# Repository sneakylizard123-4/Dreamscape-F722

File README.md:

# Dreamscape F722
Dreamscape F722 is an open-hardware STM32-based flight controller designed for FPV and custom drone platforms. It targets high-performance firmware such as Betaflight, iNav, and ArduPilot while remaining developer-friendly for experimentation and customization. The design focuses on a powerful MCU, robust connectivity, and support for a wide range of peripherals to enable advanced flight control features and future expansion.

# Features
## MCU
- STM32 F722RET6
- 32-bit ARM Cortex-M7 CPU
- Up to 216 MHz clock speed
- Large memory for advanced firmware features
- Compatible with Betaflight/iNav/ArduPilot

## Power System
- 5V input with built-in 3.3v regulator
- Power distribution for peripherals
- USB Power support
- Protection for USB

## Connectivity
- USB Type-C for programming and communication
- Multiple UART ports for telemetry and peripherals
- I2C bus for sensors and accessories
- SPI interface for high-speed communication
- SWD debugging port

## Sensors
- ICM-42688-P 6-axis IMU (3-axis gyroscope + 3-axis accelerometer) via SPI for precise flight control and low latency
- BMP280 barometer for altitude sensing
- Optional external sensor support via I2C

## Flight Control Outputs
- 8 PWM outputs
- Supports DSHOT, Oneshot, and standard PWM protocols
- Compatible with individual ESCs or 4-in-1 ESCs

## Radio / Receiver Support
- CRSF (Crossfire) support for long-range control
- SBUS support for standard RC receivers
- PPM support for legacy receivers
- Support for external radio modules via UART

## Status & Indicators
- Power LED
- User LED
- Boot/Status LED

## Expansion & Peripherals
- GPS module support via UART
- Telemetry Radios
- VTX control (SmartAudio or Tramp)
- Buzzer for audible alerts
- Camera control
- External sensor support (e.g., magnetometer, external barometer)

## Physical Design
- Compact flight-controller form factor (30x30mm)
- Standard mounting pattern
- Designed for custom drones

## Development Friendly
- Open-source hardware design files
- Open-source firmware support (Betaflight, iNav, ArduPilot)
- Easy debugging with SWD port

## Planned Future Features
- Integrated ELRS receiver
- Dual-Band telemetry support
- Advanced Sensor suite
- Power monitoring improvements
- Integrated OSD support

# Specifications
## Core Specifications
### MCU
- MCU: STM32 F722RET6
- Architecture: ARM Cortex-M7
- Clock Speed: Up to 216 MHz
- Flash Memory: 512 KB
- RAM: 256 KB
- Hardware Floating Point Unit (FPU)

### Inertial Measurement Unit (IMU)
- IMU: ICM-42688-P
- HIgh-speed SPI bus for low latency
- Optimied placement for reduced vibration noise

### Power System
- Input Voltage: 5V (via USB or power distribution)
- Built-in 3.3V regulator for peripherals
- USB Power support with protection
- Power distribution for connected peripherals

## I/O and Connectivity
### UART Ports
- UART1: Receiver 
- UART2: GPS module
- UART3: Telemetry
- UART4: VTX Control
- UART5: Reserved for future expansion

### SPI Interfaces
- SPI1: IMU (ICM-42688-P)
- SPI2: Reserved for future sensor expansion

### I2C Bus
- I2C bus available for peripherals such as magnetometers, external barometers, etc.

### SWD
- SWD header for debugging and firmware development

## Motor Outputs
- Up to 8 PWM outputs
- Suppored Protocols:
  - DShot150/300/600
  - OneShot
  - Multishot
  - Standard PWM
  - Compatible with individual ESCs or 4-in-1 ESCs

## Receiver Support
- CRSF (Crossfire) support for long-range control
- SBUS support for standard RC receivers
- PPM support for legacy receivers
- Support for external radio modules via UART

## Additional Peripherals
- Buzzer output
- LED Strip output
- Camera control
- VTX control (SmartAudio or Tramp)

## Status Indicators
- Power LED
- User LED
- Boot/Status LED

## Physical Dimensions
- Size: 30x30mm
- Board Layers: 4
- PCB Thickness: 1.6mm
- Copper Weight: 1oz
- Dimensions: Standard flight controller mounting pattern

## Firmware Compatibility
- Designed for compatibility with Betaflight, iNav, and ArduPilot
- Open-source firmware support for customization and development

## Development Features
- Open Hardware design
- Full SWD debugging support
- Compatible with ST-Link Programmers
- Designed for experimentation and customization

## Planned Future Features
- Integrated ELRS receiver for long-range control
- Dual-Band telemetry support for improved communication
- Advanced Sensor suite including magnetometer and external barometer support
- Integrated ESC for AIO support
- Integrated OSD support for on-screen display of flight information
- Improved powwer monitoring with current sensing and voltage monitoring

# Firmware Building
````bash
cd ~/Dreamscape-F722/firmware/betaflight/betaflight
make configs
make DREAMSCAPEF722
````

# Blender Render:

# Schematics & PCB view

# prices

# LCSC (Hand Soldering)

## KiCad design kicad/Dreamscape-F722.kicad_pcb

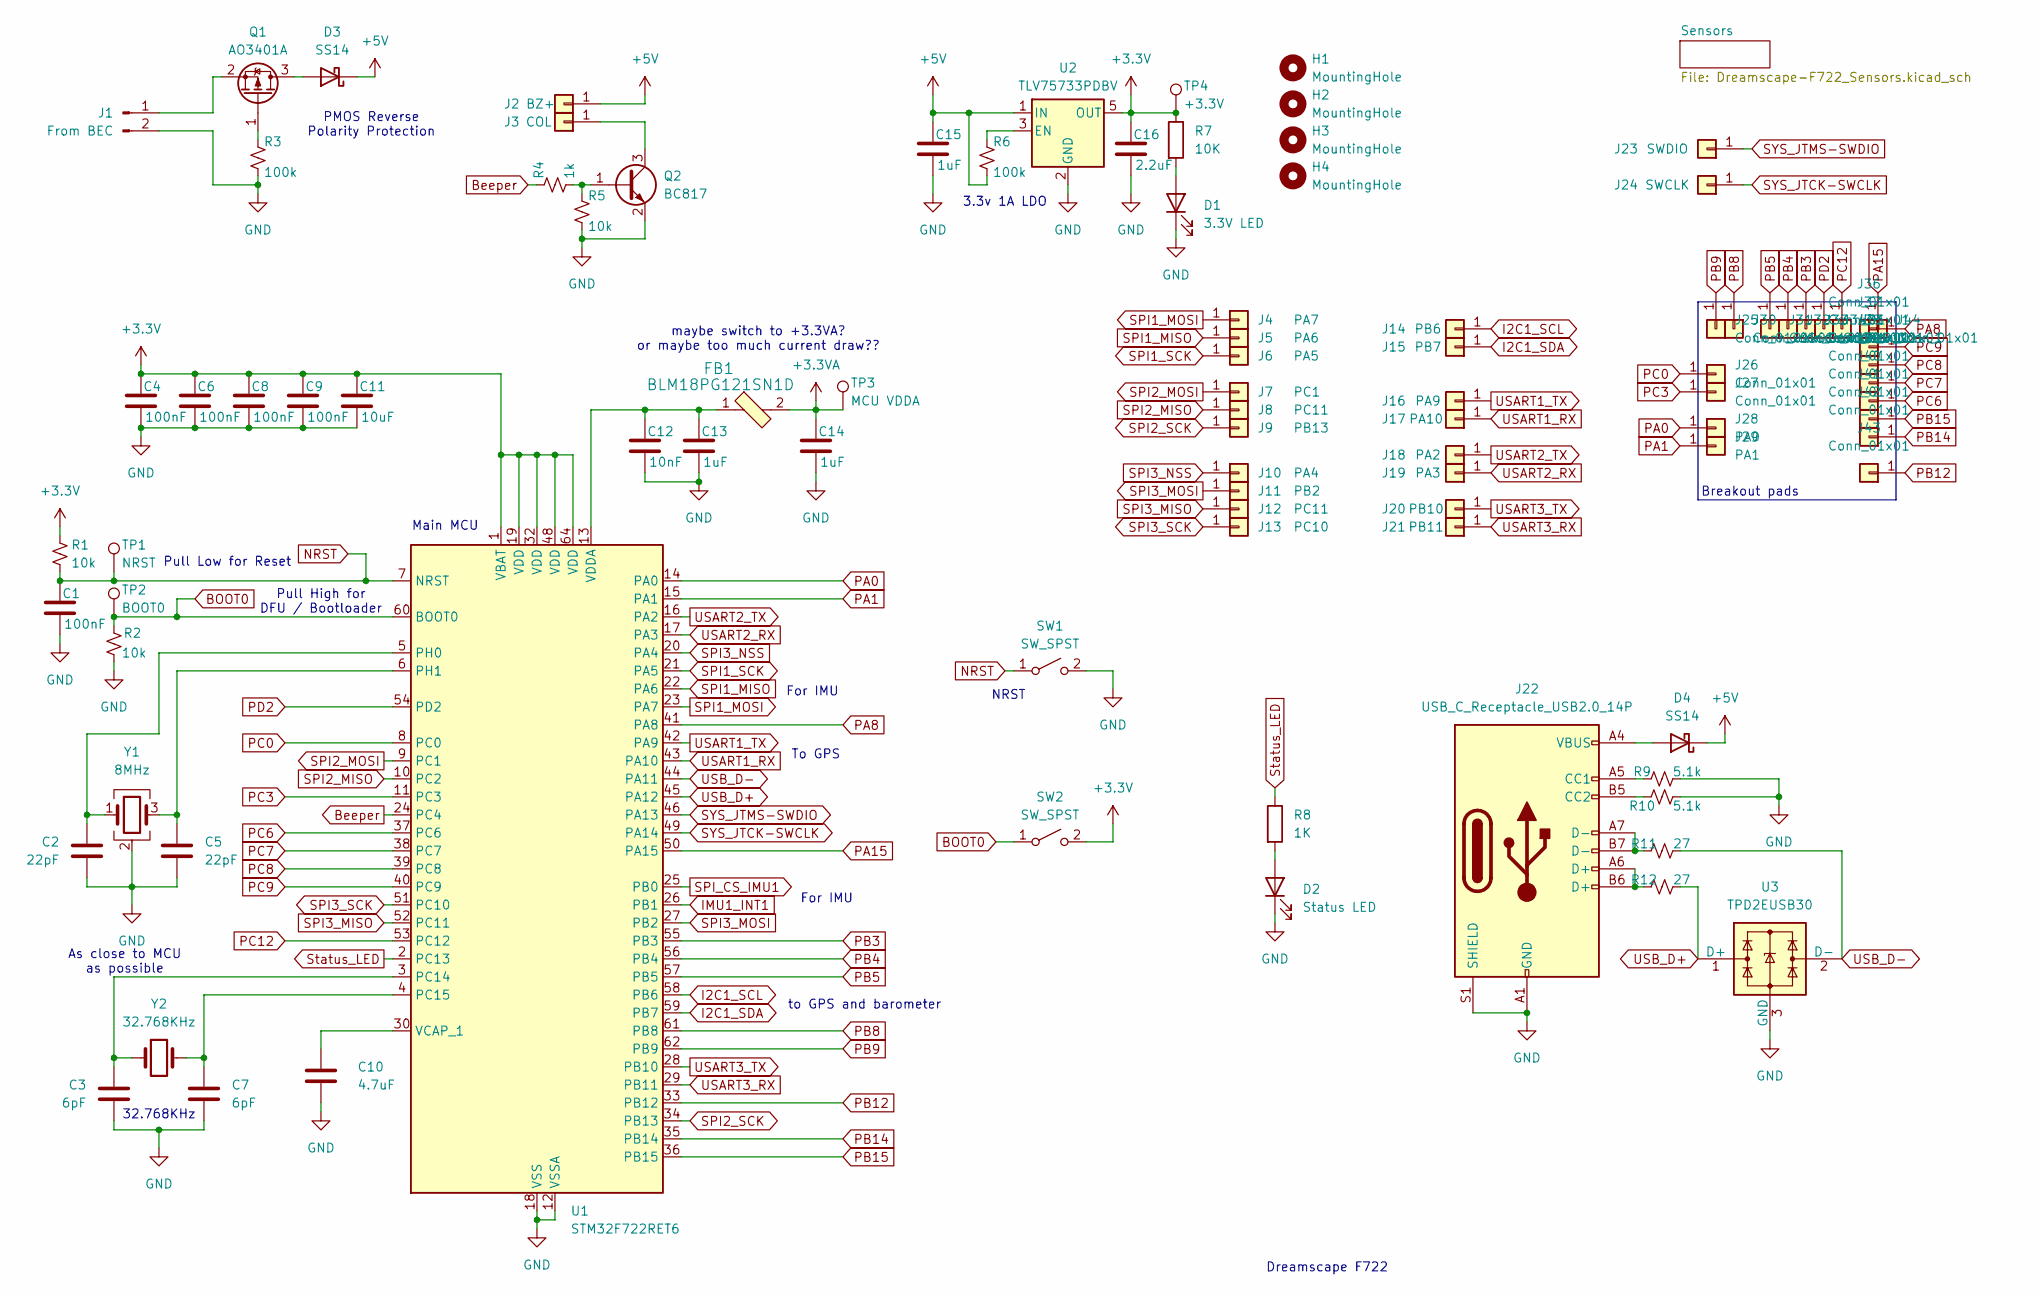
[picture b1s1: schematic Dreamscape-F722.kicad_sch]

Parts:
C1: 100nF; C_0603_1608Metric_Pad1.08x0.95mm_HandSolder
C2, C5: 22pF; C_0603_1608Metric
C3, C7: 6pF; C_0603_1608Metric
C4, C6, C8, C9: 100nF; C_0402_1005Metric_Pad0.74x0.62mm_HandSolder
C10: 4.7uF; C_0603_1608Metric_Pad1.08x0.95mm_HandSolder
C11: 10uF; C_0603_1608Metric_Pad1.08x0.95mm_HandSolder
C12: 10nF; C_0402_1005Metric_Pad0.74x0.62mm_HandSolder
C13, C14: 1uF; C_0402_1005Metric_Pad0.74x0.62mm_HandSolder
C15: 1uF; C_0603_1608Metric_Pad1.08x0.95mm_HandSolder
C16: 2.2uF; C_0603_1608Metric_Pad1.08x0.95mm_HandSolder
D1: 3.3V LED; LED_0603_1608Metric
D2: Status LED; LED_0603_1608Metric_Pad1.05x0.95mm_HandSolder
D3, D4: SS14; D_SMA
FB1: BLM18PG121SN1D; 0603; MPN BLM18PG121SN1D; Digi-Key_PN 490-1037-1-ND
H1, H2, H3, H4: MountingHole; MountingHole_3.2mm_M3
J1: From BEC; Hirose_DF13-02P-1.25DS_1x02_P1.25mm_Horizontal
J2: BZ+; SolderWirePad_1x01_SMD_1x2mm
J3: COL; SolderWirePad_1x01_SMD_1x2mm
J4: PA7; SolderWirePad_1x01_SMD_1x2mm
J5: PA6; SolderWirePad_1x01_SMD_1x2mm
J6: PA5; SolderWirePad_1x01_SMD_1x2mm
J7: PC1; SolderWirePad_1x01_SMD_1x2mm
J8, J12: PC11; SolderWirePad_1x01_SMD_1x2mm
J9: PB13; SolderWirePad_1x01_SMD_1x2mm
J10: PA4; SolderWirePad_1x01_SMD_1x2mm
J11: PB2; SolderWirePad_1x01_SMD_1x2mm
J13: PC10; SolderWirePad_1x01_SMD_1x2mm
J14: PB6; SolderWirePad_1x01_SMD_1x2mm
J15: PB7; SolderWirePad_1x01_SMD_1x2mm
J16: PA9; SolderWirePad_1x01_SMD_1x2mm
J17: PA10; SolderWirePad_1x01_SMD_1x2mm
J18: PA2; SolderWirePad_1x01_SMD_1x2mm
J19: PA3; SolderWirePad_1x01_SMD_1x2mm
J20: PB10; SolderWirePad_1x01_SMD_1x2mm
J21: PB11; SolderWirePad_1x01_SMD_1x2mm
J22: USB_C_Receptacle_USB2.0_14P; USB_C_Receptacle_HRO_TYPE-C-31-M-12
J23: SWDIO; SolderWirePad_1x01_SMD_1x2mm
J24: SWCLK; SolderWirePad_1x01_SMD_1x2mm
J25, J26, J27, J30, J31, J32, J33, J34, J35, J36, J37, J38, J39, J40, J41, J42, J43, J44: Conn_01x01; SolderWirePad_1x01_SMD_1x2mm
J28: PA0; SolderWirePad_1x01_SMD_1x2mm
J29: PA1; SolderWirePad_1x01_SMD_1x2mm
Q1: AO3401A; SOT-23
Q2: BC817; SOT-23-3
R1, R2, R5: 10k; R_0603_1608Metric_Pad0.98x0.95mm_HandSolder
R3, R6: 100k; R_0603_1608Metric_Pad0.98x0.95mm_HandSolder
R4: 1k; R_0603_1608Metric_Pad0.98x0.95mm_HandSolder
R7: 10K; R_0603_1608Metric_Pad0.98x0.95mm_HandSolder
R8: 1K; R_0603_1608Metric_Pad0.98x0.95mm_HandSolder
R9, R10: 5.1k; R_0402_1005Metric_Pad0.72x0.64mm_HandSolder
R11, R12: 27; R_0402_1005Metric_Pad0.72x0.64mm_HandSolder
SW1, SW2: SW_SPST; SW_SPST_B3U-3000P
TP1: NRST; TestPoint_Pad_1.0x1.0mm
TP2: BOOT0; TestPoint_Pad_1.0x1.0mm
TP3: MCU VDDA; TestPoint_Pad_1.0x1.0mm
TP4: +3.3V; TestPoint_Pad_1.0x1.0mm
U1: STM32F722RET6; LQFP-64_10x10mm_P0.5mm
U2: TLV75733PDBV; SOT-23-5
U3: TPD2EUSB30; Texas_DRT-3
Y1: 8MHz; Crystal_SMD_3225-4Pin_3.2x2.5mm; LCSC C2905353
Y2: 32.768KHz; Crystal_SMD_2012-2Pin_2.0x1.2mm; LCSC C99009

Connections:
+3.3V: C4.1, C6.1, C8.1, C9.1, C11.1, C16.1, R1.1, R7.1, SW2.2 (B), TP4.1, U1.1 (VBAT), U1.19 (VDD), U1.32 (VDD), U1.48 (VDD), U1.64 (VDD), U2.5 (OUT); also elsewhere on the board
+3.3VA: C14.1, FB1.2, TP3.1
+5V: C15.1, D3.1 (K), D4.1 (K), J2.1, R6.2, U2.1 (IN)
BOOT0: R2.1, SW2.1 (A), TP2.1, U1.60 (BOOT0)
Beeper: R4.1, U1.24 (PC4)
GND: C1.2, C2.2, C3.2, C4.2, C5.2, C6.2, C7.2, C8.2, C9.2, C10.2, C11.2, C12.2, C13.2, C14.2, C15.2, C16.2, D1.1 (K), D2.1 (K), J1.2, J22.A1 (GND), J22.A12 (GND), J22.B1 (GND), J22.B12 (GND), J22.S1 (SHIELD), Q2.2 (E), R2.2, R3.2, R5.2, R9.2, R10.1, SW1.2 (B), U1.12 (VSSA), U1.18 (VSS), U1.31 (VSS), U1.47 (VSS), U1.63 (VSS), U2.2 (GND), U3.3 (GND), Y1.2 (G), Y1.4 (G); also elsewhere on the board
I2C1_SCL: J14.1, U1.58 (PB6); also elsewhere on the board
I2C1_SDA: J15.1, U1.59 (PB7); also elsewhere on the board
IMU1_INT1: U1.26 (PB1); also elsewhere on the board
NRST: C1.1, R1.2, SW1.1 (A), TP1.1, U1.7 (NRST)
unnamed: D1.2 (A), R7.2
unnamed: D2.2 (A), R8.2
unnamed: D3.2 (A), Q1.3 (D)
unnamed: D4.2 (A), J22.A4 (VBUS), J22.A9 (VBUS), J22.B4 (VBUS), J22.B9 (VBUS)
unnamed: J1.1, Q1.2 (S)
unnamed: J3.1, Q2.3 (C)
unnamed: J22.A5 (CC1), R9.1
unnamed: J22.B5 (CC2), R10.2
unnamed: J22.A6 (D+), J22.B6 (D+), R12.2
unnamed: J22.A7 (D-), J22.B7 (D-), R11.1
unnamed: Q1.1 (G), R3.1
unnamed: Q2.1 (B), R4.2, R5.1
unnamed: C3.1, U1.3 (PC14), Y2.1
unnamed: C7.1, U1.4 (PC15), Y2.2
unnamed: C2.1, U1.5 (PH0), Y1.1
unnamed: C5.1, U1.6 (PH1), Y1.3
unnamed: C10.1, U1.30 (VCAP_1)
unnamed: C12.1, C13.1, FB1.1, U1.13 (VDDA)
unnamed: R6.1, U2.3 (EN)
PA0: J28.1, U1.14 (PA0)
PA1: J29.1, U1.15 (PA1)
PA8: J36.1, U1.41 (PA8)
PA15: J44.1, U1.50 (PA15)
PB3: J33.1, U1.55 (PB3)
PB4: J32.1, U1.56 (PB4)
PB5: J31.1, U1.57 (PB5)
PB8: J30.1, U1.61 (PB8)
PB9: J25.1, U1.62 (PB9)
PB12: J43.1, U1.33 (PB12)
PB14: J42.1, U1.35 (PB14)
PB15: J41.1, U1.36 (PB15)
PC0: J26.1, U1.8 (PC0)
PC3: J27.1, U1.11 (PC3)
PC6: J40.1, U1.37 (PC6)
PC7: J39.1, U1.38 (PC7)
PC8: J38.1, U1.39 (PC8)
PC9: J37.1, U1.40 (PC9)
PC12: J35.1, U1.53 (PC12)
PD2: J34.1, U1.54 (PD2)
SPI1_MISO: J5.1, U1.22 (PA6); also elsewhere on the board
SPI1_MOSI: J4.1, U1.23 (PA7); also elsewhere on the board
SPI1_SCK: J6.1, U1.21 (PA5); also elsewhere on the board
SPI2_MISO: J8.1, U1.10 (PC2)
SPI2_MOSI: J7.1, U1.9 (PC1)
SPI2_SCK: J9.1, U1.34 (PB13)
SPI3_MISO: J12.1, U1.52 (PC11)
SPI3_MOSI: J11.1, U1.27 (PB2)
SPI3_NSS: J10.1, U1.20 (PA4)
SPI3_SCK: J13.1, U1.51 (PC10)
SPI_CS_IMU1: U1.25 (PB0); also elsewhere on the board
SYS_JTCK-SWCLK: J24.1, U1.49 (PA14)
SYS_JTMS-SWDIO: J23.1, U1.46 (PA13)
Status_LED: R8.1, U1.2 (PC13)
USART1_RX: J17.1, U1.43 (PA10)
USART1_TX: J16.1, U1.42 (PA9)
USART2_RX: J19.1, U1.17 (PA3)
USART2_TX: J18.1, U1.16 (PA2)
USART3_RX: J21.1, U1.29 (PB11)
USART3_TX: J20.1, U1.28 (PB10)
USB_D+: R12.1, U1.45 (PA12), U3.1 (D+)
USB_D-: R11.2, U1.44 (PA11), U3.2 (D-)

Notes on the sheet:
Breakout pads
3.3v 1A LDO
PMOS Reverse Polarity Protection
To GPS
maybe switch to +3.3VA? or maybe too much current draw??
Dreamscape F722
Pull High for DFU / Bootloader
32.768KHz
As close to MCU as possible
to GPS and barometer
For IMU
Pull Low for Reset
Main MCU
NRST

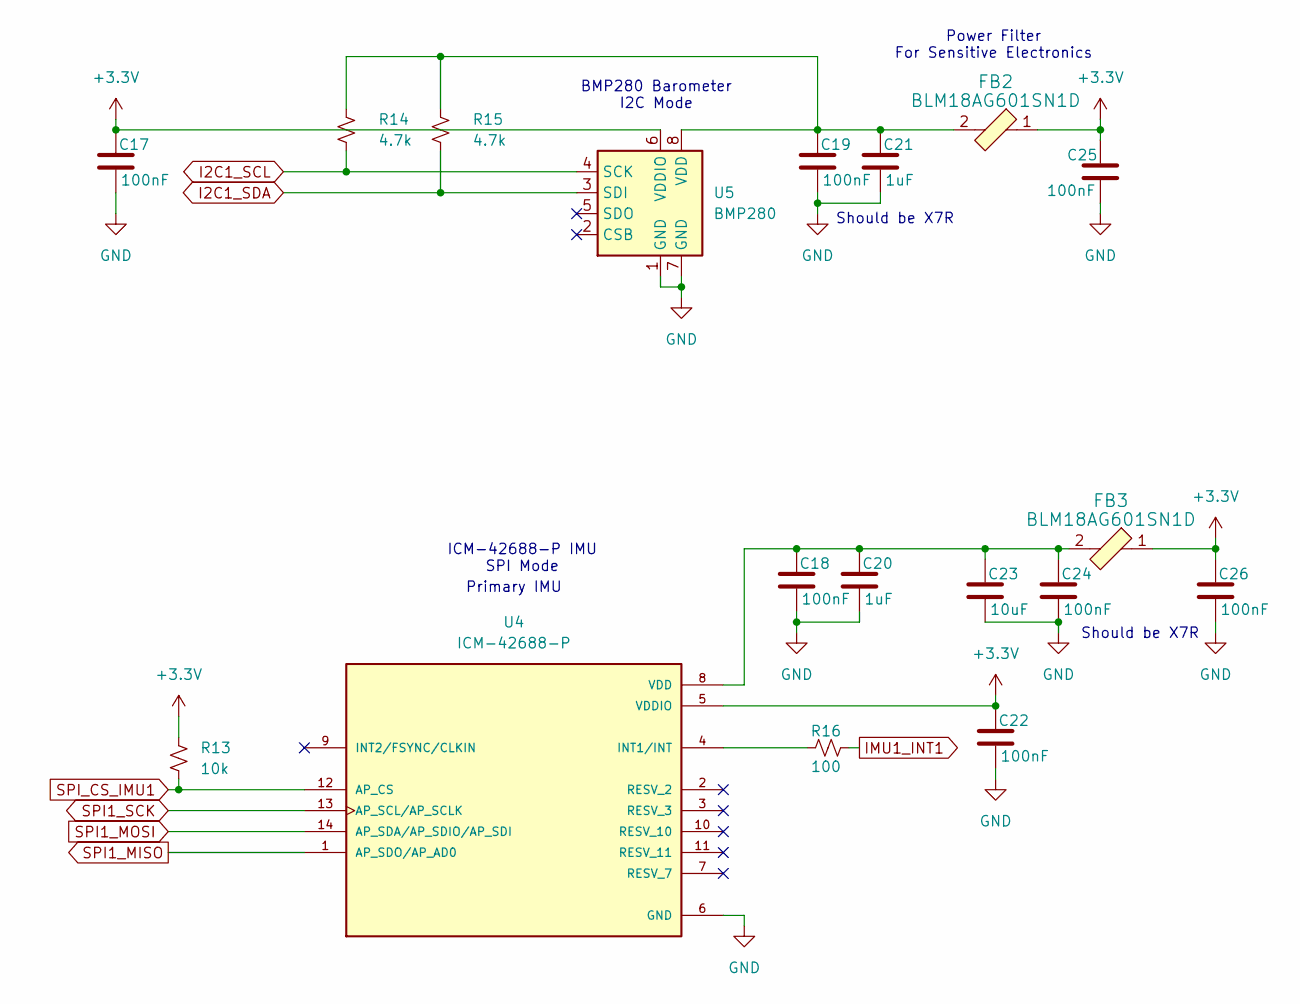
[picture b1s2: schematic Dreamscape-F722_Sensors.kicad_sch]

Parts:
C17, C18, C19, C22: 100nF; C_0402_1005Metric_Pad0.74x0.62mm_HandSolder
C20, C21: 1uF; C_0402_1005Metric_Pad0.74x0.62mm_HandSolder
C23: 10uF; C_0603_1608Metric_Pad1.08x0.95mm_HandSolder
C24, C25, C26: 100nF; C_0603_1608Metric_Pad1.08x0.95mm_HandSolder
FB2, FB3: BLM18AG601SN1D; 0603; MPN BLM18AG601SN1D; Digi-Key_PN 490-1014-1-ND
R13: 10k; R_0603_1608Metric_Pad0.98x0.95mm_HandSolder
R14, R15: 4.7k; R_0603_1608Metric_Pad0.98x0.95mm_HandSolder
R16: 100; R_0603_1608Metric_Pad0.98x0.95mm_HandSolder
U4: ICM-42688-P; PQFN50P300X250X97-14N; PARTREV 1.2
U5: BMP280; Bosch_LGA-8_2x2.5mm_P0.65mm_ClockwisePinNumbering

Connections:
+3.3V: C17.1, C22.1, C25.1, C26.1, FB2.1, FB3.1, R13.2, U4.5 (VDDIO), U5.6 (VDDIO); also elsewhere on the board
GND: C17.2, C18.2, C19.2, C20.2, C21.2, C22.2, C23.2, C24.2, C25.2, C26.2, U4.6 (GND), U5.1 (GND), U5.7 (GND); also elsewhere on the board
I2C1_SCL: R14.2, U5.4 (SCK); also elsewhere on the board
I2C1_SDA: R15.2, U5.3 (SDI); also elsewhere on the board
IMU1_INT1: R16.2; also elsewhere on the board
unnamed: R16.1, U4.4 (INT1/INT)
unnamed: C18.1, C20.1, C23.1, C24.1, FB3.2, U4.8 (VDD)
unnamed: C19.1, C21.1, FB2.2, R14.1, R15.1, U5.8 (VDD)
SPI1_MISO: U4.1 (AP_SDO/AP_AD0); also elsewhere on the board
SPI1_MOSI: U4.14 (AP_SDA/AP_SDIO/AP_SDI); also elsewhere on the board
SPI1_SCK: U4.13 (AP_SCL/AP_SCLK); also elsewhere on the board
SPI_CS_IMU1: R13.1, U4.12 (AP_CS); also elsewhere on the board

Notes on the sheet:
Power Filter For Sensitive Electronics
Should be X7R
Primary IMU
BMP280 Barometer I2C Mode
ICM-42688-P IMU SPI Mode

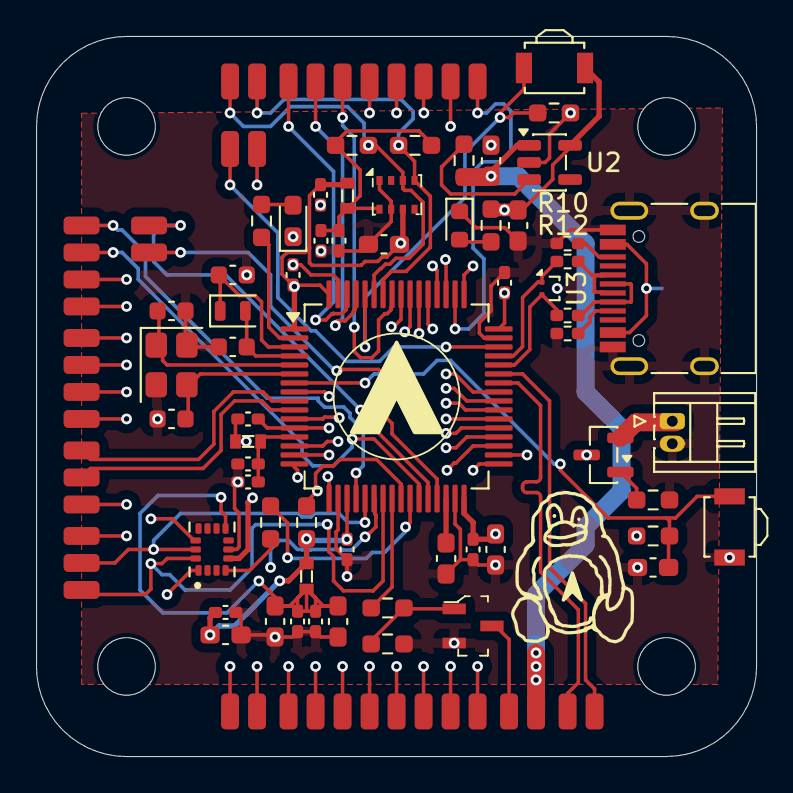
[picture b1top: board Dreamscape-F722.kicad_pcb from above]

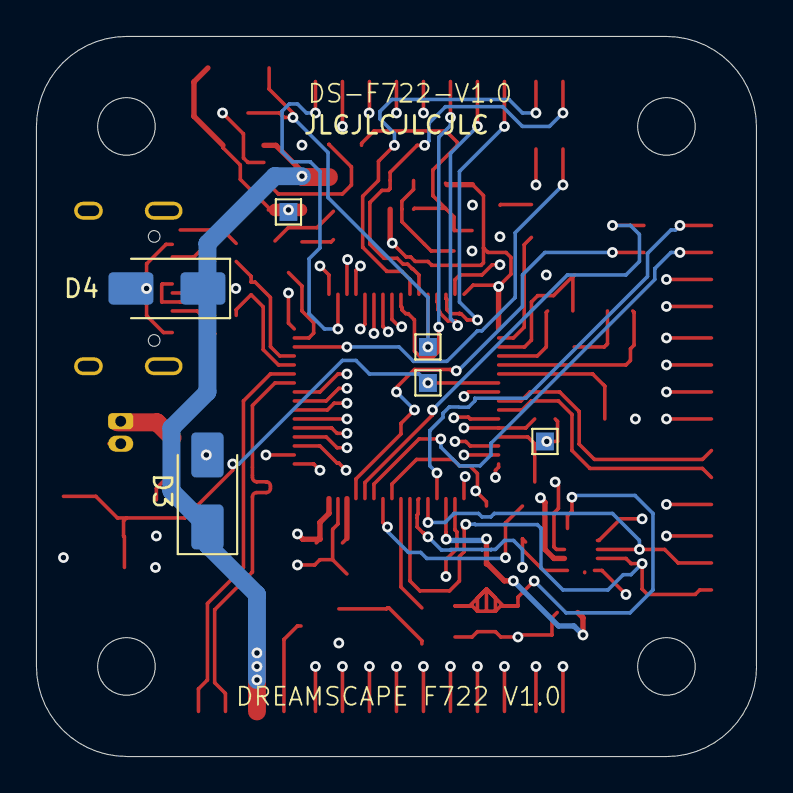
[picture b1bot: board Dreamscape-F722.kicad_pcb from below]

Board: 4 copper layers, 40.0 x 40.0 mm, 112 parts (6 on the bottom side), 74 nets.

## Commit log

2026-01-09 Update README with schematics and pricing images
    Added schematics, PCB views, and pricing images.
2026-01-09 optimise more
2026-01-21 add custom parts
2026-01-21 add bec schematic
2026-01-21 switch to stm32
2026-01-24 add new part
2026-01-24 move BEC to new sheet
2026-01-24 move sensors to new sheet
2026-01-24 add gps module
2026-01-24 add mosfet ao4435
2026-01-25 organise esc schematic
2026-01-25 motors 3 and 4, esc
2026-01-25 df13 connectors and more connectors for the bec
2026-01-26 motor esc schematics
2026-01-27 prepare to move esc, gps, bec to other project
2026-01-27 BEC has been moved to its own project
2026-01-27 GPS has been moved to its own project
2026-01-29 remove bec and gps
2026-02-04 add pcb3d
2026-02-04 remove unnecessary parts
2026-02-04 remove unnecessary schematics
2026-02-04 ready for production almost
2026-02-04 add .blend file
2026-02-04 fix drc issues and blender render
2026-02-04 better blender lighting?
2026-02-04 update pictures
2026-02-04 try to add images
2026-02-04 add price
2026-02-05 firmware and readme
2026-02-05 remove old images
2026-02-05 add images
2026-02-05 new gerbers
2026-02-06 add switches and fix drc
2026-02-07 add buttons and fix drc
2026-02-08 added ICM-42688-P IMU
2026-02-08 switch imu and barometer
2026-02-09 restart pcb because too many new parts
2026-02-11 ready for ship
2026-02-11 update images in readme
2026-02-12 it came to me in a dream
2026-02-12 dreams
2026-02-12 add ground plane
2026-02-12 beef up power traces
2026-02-12 optimise trace placement
2026-02-12 add Dreamscape F722 Silkscreen
2026-02-12 Dreamscape F722 in README
2026-02-12 rename files
2026-02-12 Update README to remove firmware details
    Removed firmware section from README.
2026-02-12 add building instructions
2026-02-12 build gerbers
2026-02-12 i opened the pcb file and i think it updated the dates
2026-02-12 add 3d model
2026-02-13 add cart images
2026-02-13 add images to readme
2026-02-13 update blender
2026-02-13 blender updates
2026-02-14 Add Purple image to Blender Render section
2026-02-17 organise files
2026-02-17 add code blocks in readme
2026-02-17 optimise traces
2026-02-20 move imported parts into kicad directory
2026-02-20 add diodes to pcb (wiring tomorrow)
2026-03-05 update repos
2026-03-06 change ldo to hand-solderable type
2026-03-07 update blenders
